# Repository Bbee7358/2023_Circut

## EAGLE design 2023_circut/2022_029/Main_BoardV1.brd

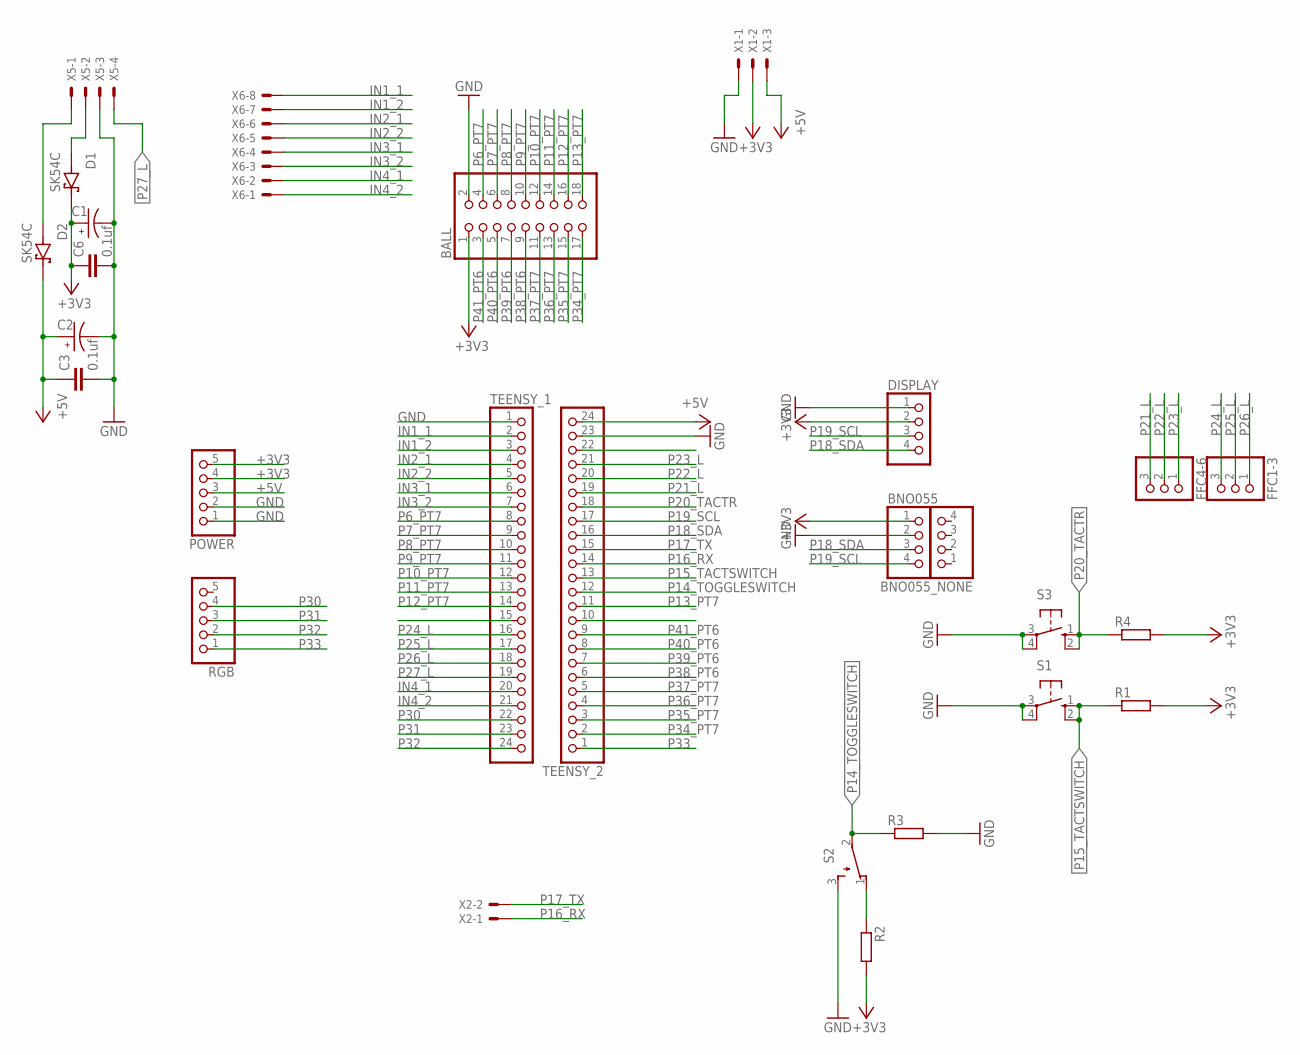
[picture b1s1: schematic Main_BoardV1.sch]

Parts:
BALL: PINHD-2X9; 2X09
BNO055, BNO055_NONE: PINHD-1X4; 1X04
C1, C2: EEEFK1E332AM; CAP_EEEFK1E332AM
C3, C6: 0.1uf; C0603
D1, D2: SK54C; DIOM6859X262N
DISPLAY: PINHD-1X04_2.54-S; 1X04-S
FFC1-3, FFC4-6: PINHD-1X03_2.54-S; 1X03-S
POWER: PINHD-1X05_2.54-S; 1X05-S
R1, R2, R3, R4: R-EU_0207/10; 0207/10
RGB: PINHD-1X05_2.54-S; 1X05-S
S1: 40-XX; B3F-40XX
S2: TL32PO; TL3XPO
S3: 10-XX; B3F-10XX
TEENSY_1, TEENSY_2: PINHD-1X24; 1X24
X1: JST-XH-03-PIN-ROUND-PAD; JST-XH-03-PACKAGE-ROUND-PAD
X2: JST-XH-02-PIN-ROUND-PAD; JST-XH-02-PACKAGE-ROUND-PAD
X5: JST-XH-04-PIN-ROUND-PAD; JST-XH-04-PACKAGE-ROUND-PAD
X6: JST-XH-08-PIN-ROUND-PAD; JST-XH-08-PACKAGE-ROUND-PAD

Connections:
+3V3: BALL.1, BNO055.1, C1.1, C6.1, D1.C (K), DISPLAY.2, POWER.4, POWER.5, R1.2, R2.2, R4.2, X1.2
+5V: C2.1, C3.1, D2.C (K), POWER.3, TEENSY_2.24, X1.3
GND: BALL.2, BNO055.2, C1.2, C2.2, C3.2, C6.2, DISPLAY.1, POWER.1, POWER.2, R3.2, S1.3, S1.4 (P1), S2.3 (S), S3.3, S3.4 (P1), TEENSY_1.1, TEENSY_2.23, X1.1, X5.3
IN1_1: TEENSY_1.2, X6.8
IN1_2: TEENSY_1.3, X6.7
IN2_1: TEENSY_1.4, X6.6
IN2_2: TEENSY_1.5, X6.5
IN3_1: TEENSY_1.6, X6.4
IN3_2: TEENSY_1.7, X6.3
IN4_1: TEENSY_1.20, X6.2
IN4_2: TEENSY_1.21, X6.1
unnamed: D1.A, X5.2
unnamed: D2.A, X5.1
unnamed: R2.1, S2.1 (O)
P6_PT7: BALL.4, TEENSY_1.8
P7_PT7: BALL.6, TEENSY_1.9
P8_PT7: BALL.8, TEENSY_1.10
P9_PT7: BALL.10, TEENSY_1.11
P10_PT7: BALL.12, TEENSY_1.12
P11_PT7: BALL.14, TEENSY_1.13
P12_PT7: BALL.16, TEENSY_1.14
P13_PT7: BALL.18, TEENSY_2.11
P14_TOGGLESWITCH: R3.1, S2.2, TEENSY_2.12
P15_TACTSWITCH: R1.1, S1.1 (S), S1.2 (S1), TEENSY_2.13
P16_RX: TEENSY_2.14, X2.1
P17_TX: TEENSY_2.15, X2.2
P18_SDA: BNO055.3, DISPLAY.4, TEENSY_2.16
P19_SCL: BNO055.4, DISPLAY.3, TEENSY_2.17
P20_TACTR: R4.1, S3.1 (S), S3.2 (S1), TEENSY_2.18
P21_L: FFC4-6.3, TEENSY_2.19
P22_L: FFC4-6.2, TEENSY_2.20
P23_L: FFC4-6.1, TEENSY_2.21
P24_L: FFC1-3.3, TEENSY_1.16
P25_L: FFC1-3.2, TEENSY_1.17
P26_L: FFC1-3.1, TEENSY_1.18
P27_L: TEENSY_1.19, X5.4
P30: RGB.4, TEENSY_1.22
P31: RGB.3, TEENSY_1.23
P32: RGB.2, TEENSY_1.24
P33: RGB.1, TEENSY_2.1
P34_PT7: BALL.17, TEENSY_2.2
P35_PT7: BALL.15, TEENSY_2.3
P36_PT7: BALL.13, TEENSY_2.4
P37_PT7: BALL.11, TEENSY_2.5
P38_PT6: BALL.9, TEENSY_2.6
P39_PT6: BALL.7, TEENSY_2.7
P40_PT6: BALL.5, TEENSY_2.8
P41_PT6: BALL.3, TEENSY_2.9

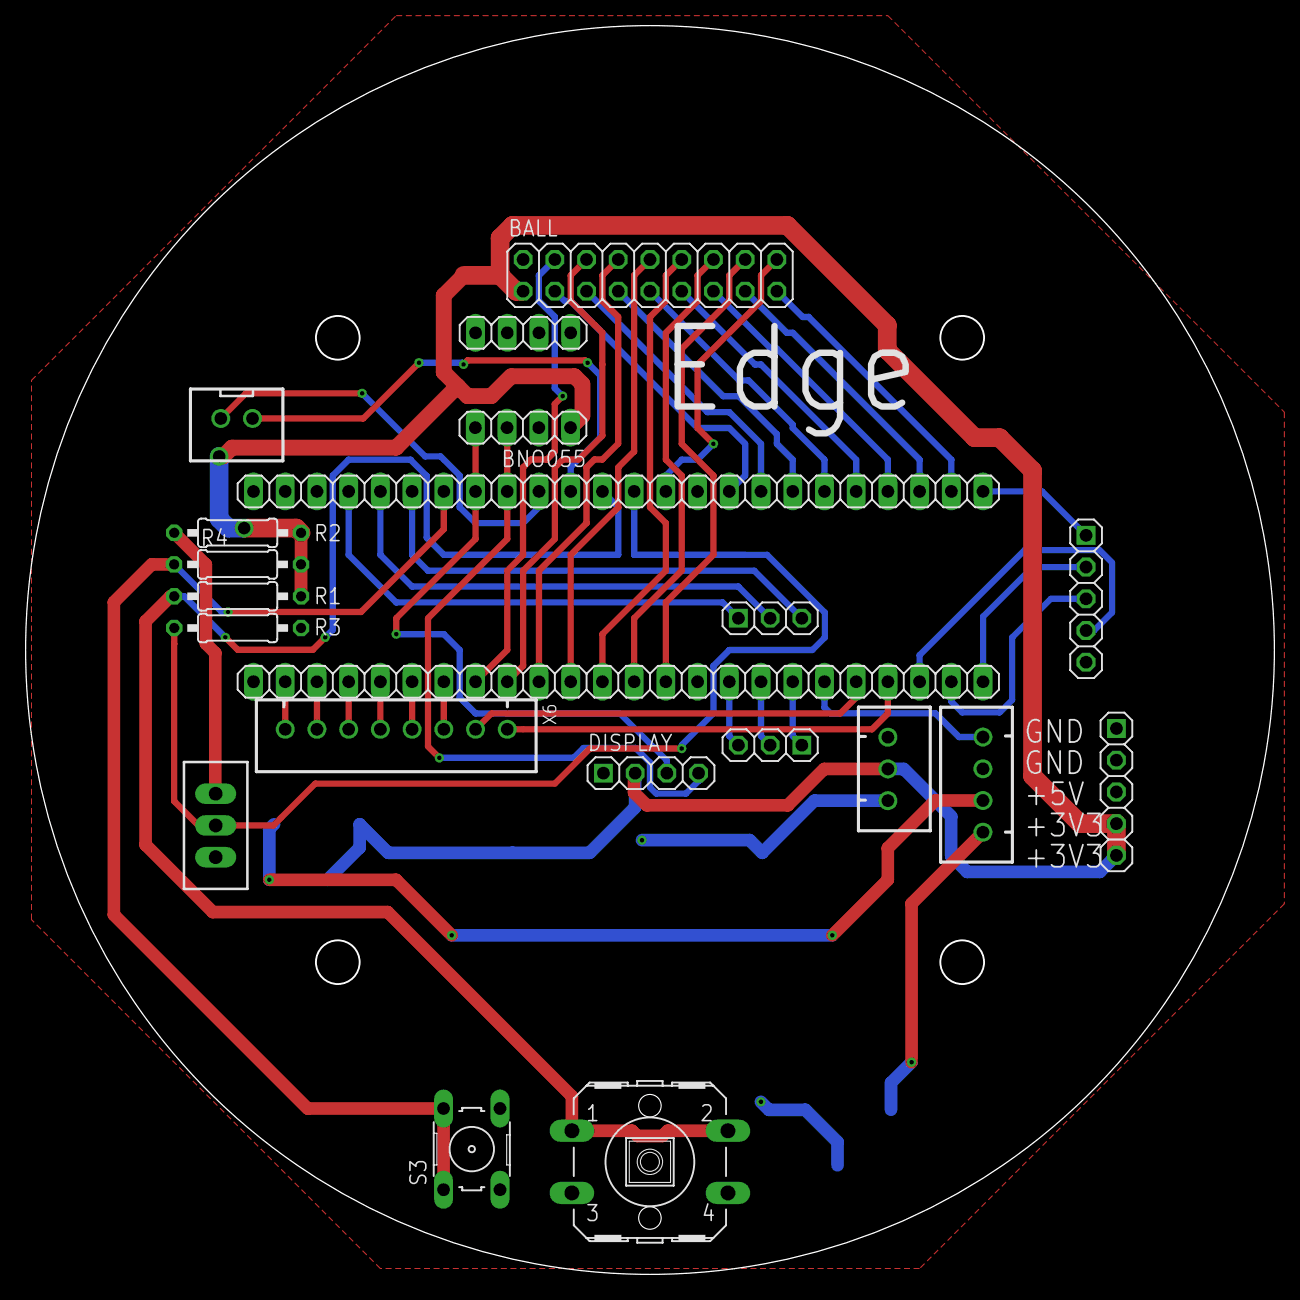
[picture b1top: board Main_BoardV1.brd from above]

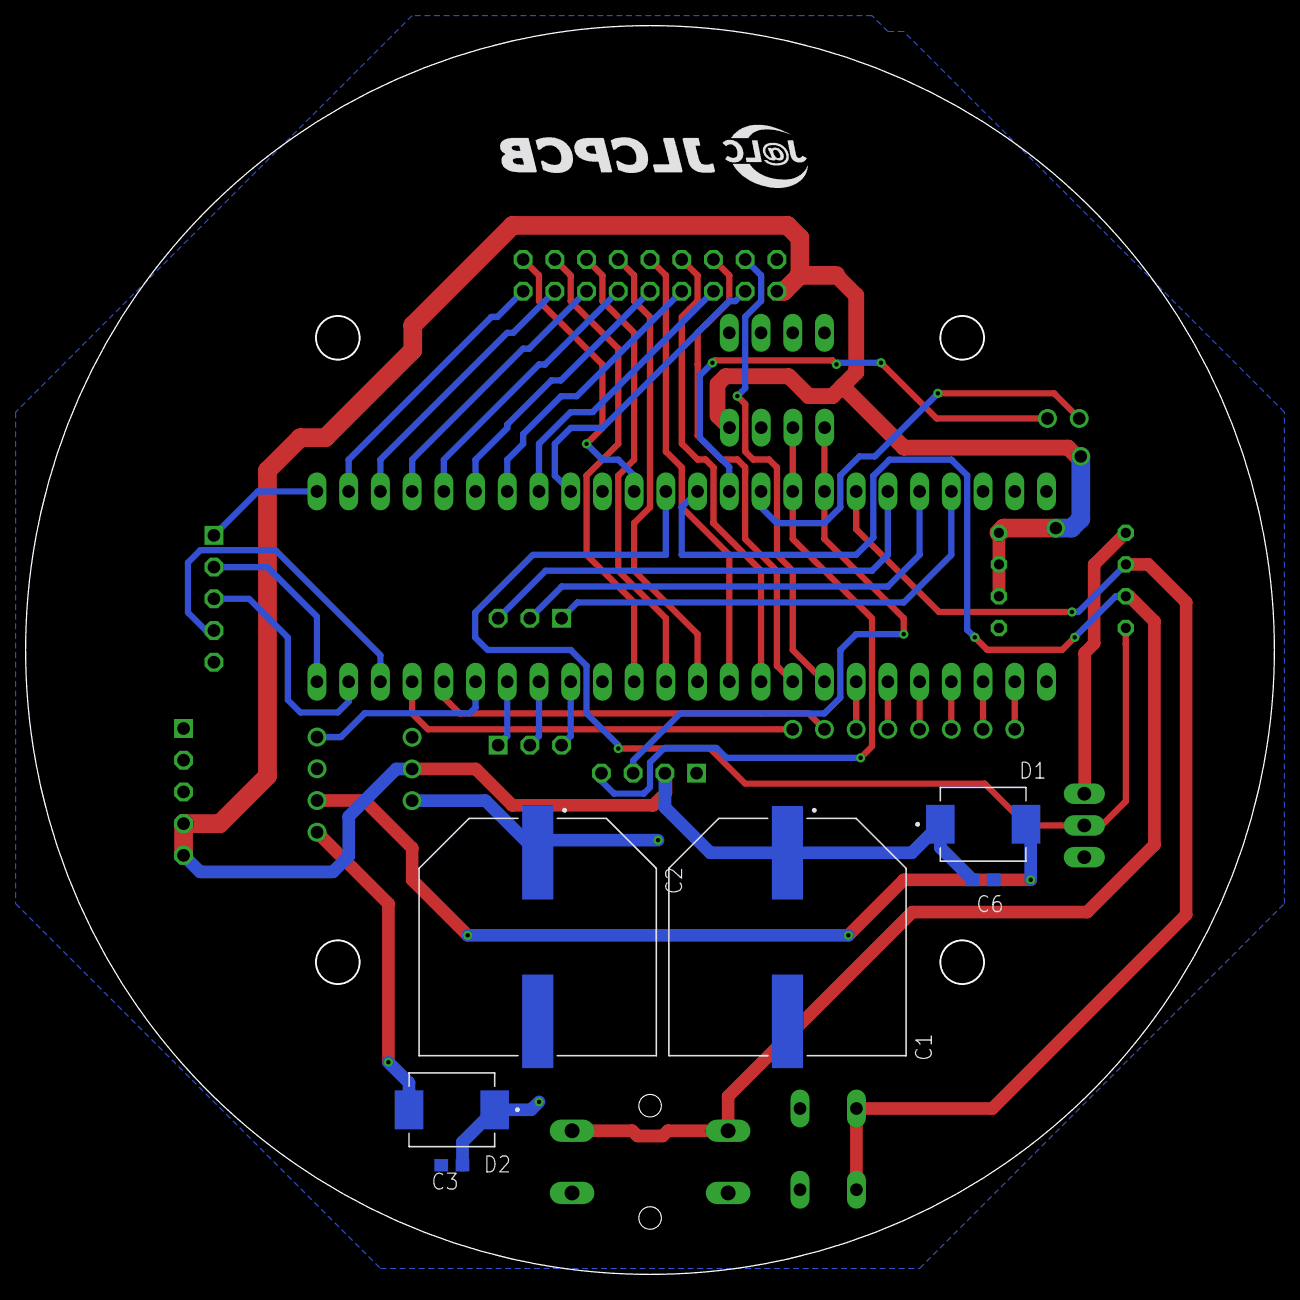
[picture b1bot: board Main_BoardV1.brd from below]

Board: 2 copper layers, 100.0 x 100.0 mm, 27 parts (6 on the bottom side), 48 nets.

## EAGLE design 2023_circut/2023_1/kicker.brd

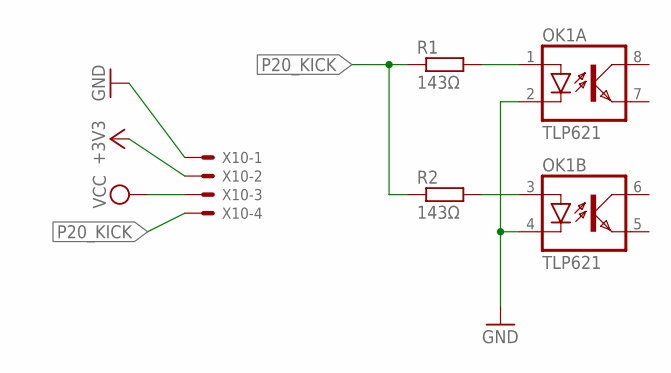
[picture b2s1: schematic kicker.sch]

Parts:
OK1: TLP621; DIL08
R1, R2: 143Ω; 0207/10
X10: Kicker; JST-XH-04-PACKAGE-ROUND-PAD

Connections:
+3V3: X10.2
GND: OK1.2 (C), OK1.4 (C), X10.1
unnamed: OK1.1 (A), R1.2
unnamed: OK1.3 (A), R2.2
P20_KICK: R1.1, R2.1, X10.4
VCC: X10.3

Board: 2 copper layers, 4 parts (0 on the bottom side), 4 nets, no tracks yet.

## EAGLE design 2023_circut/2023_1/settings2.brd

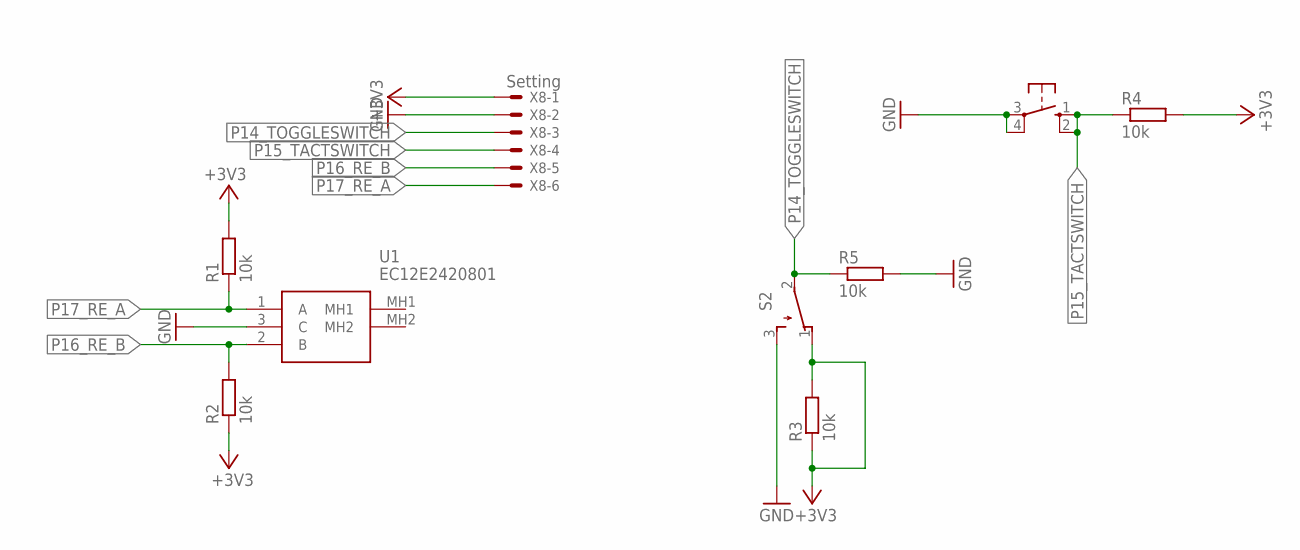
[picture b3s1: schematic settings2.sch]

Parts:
R1, R2, R3, R4, R5: 10k; R0603
S1: 40-XX; B3F-40XX
S2: TL32PO; TL3XPO
U1: EC12E2420801
X8: Setting; JST-XH-06-PACKAGE-ROUND-PAD

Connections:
+3V3: R1.2, R2.1, R3.1, R3.2, R4.2, S2.1 (O), X8.1
GND: R5.2, S1.3, S1.4 (P1), S2.3 (S), U1.3 (C), X8.2
P14_TOGGLESWITCH: R5.1, S2.2, X8.3
P15_TACTSWITCH: R4.1, S1.1 (S), S1.2 (S1), X8.4
P16_RE_B: R2.2, U1.2 (B), X8.5
P17_RE_A: R1.1, U1.1 (A), X8.6

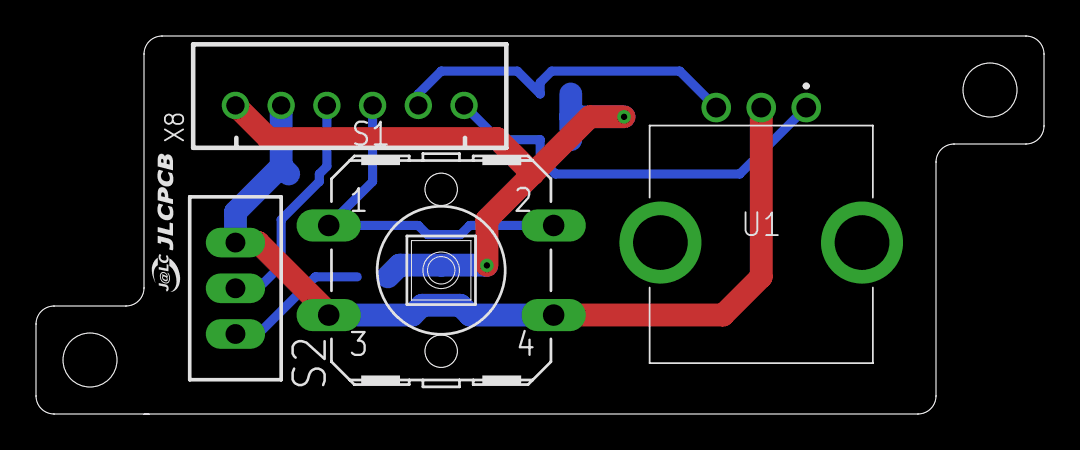
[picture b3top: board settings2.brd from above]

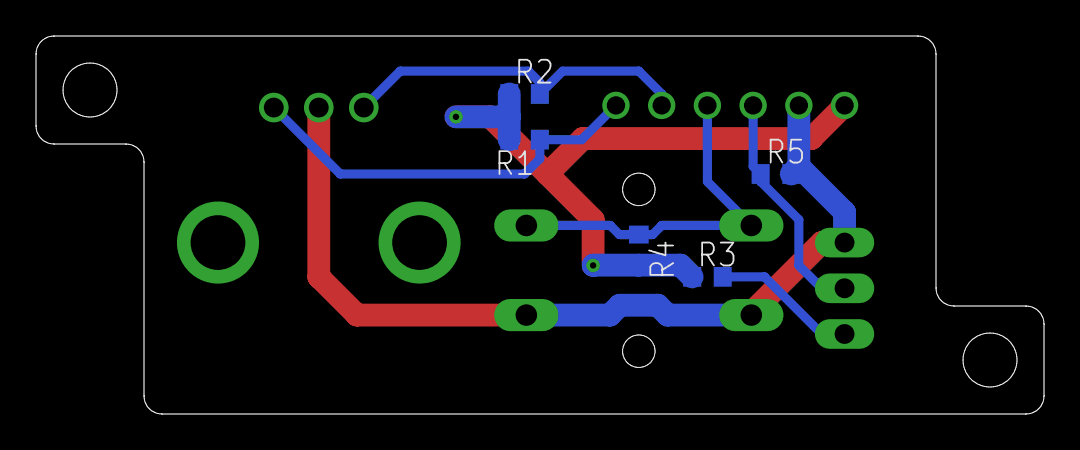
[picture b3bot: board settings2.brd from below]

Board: 2 copper layers, 56.0 x 21.0 mm, 9 parts (5 on the bottom side), 6 nets.
